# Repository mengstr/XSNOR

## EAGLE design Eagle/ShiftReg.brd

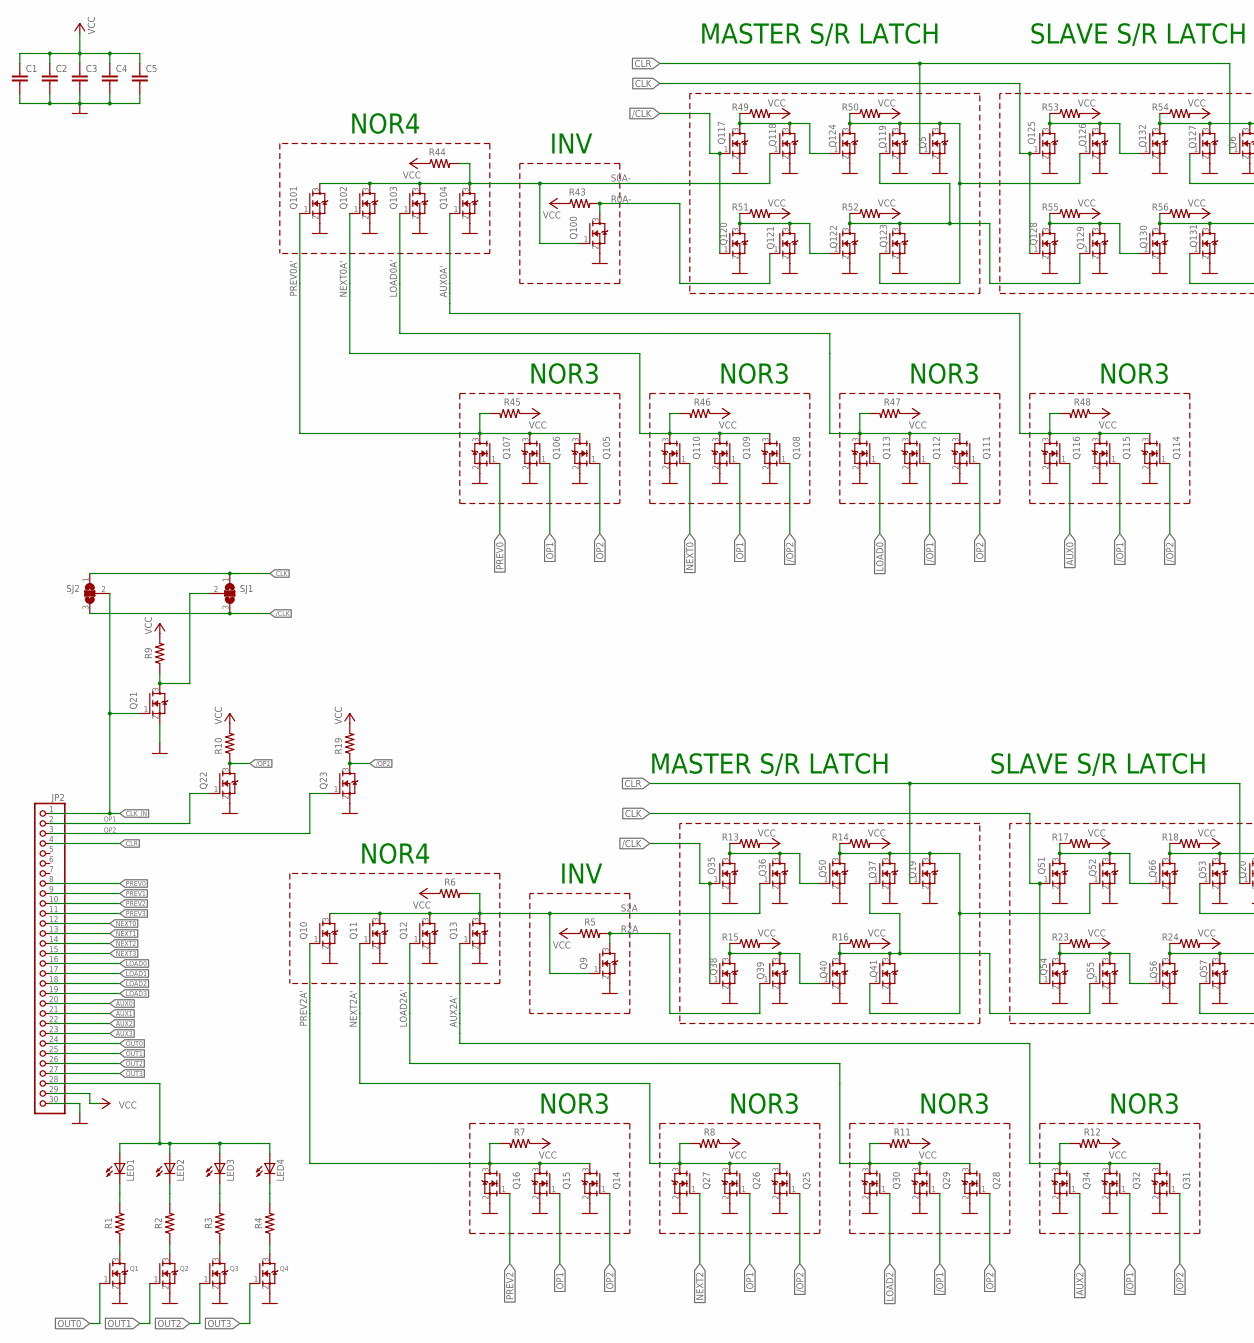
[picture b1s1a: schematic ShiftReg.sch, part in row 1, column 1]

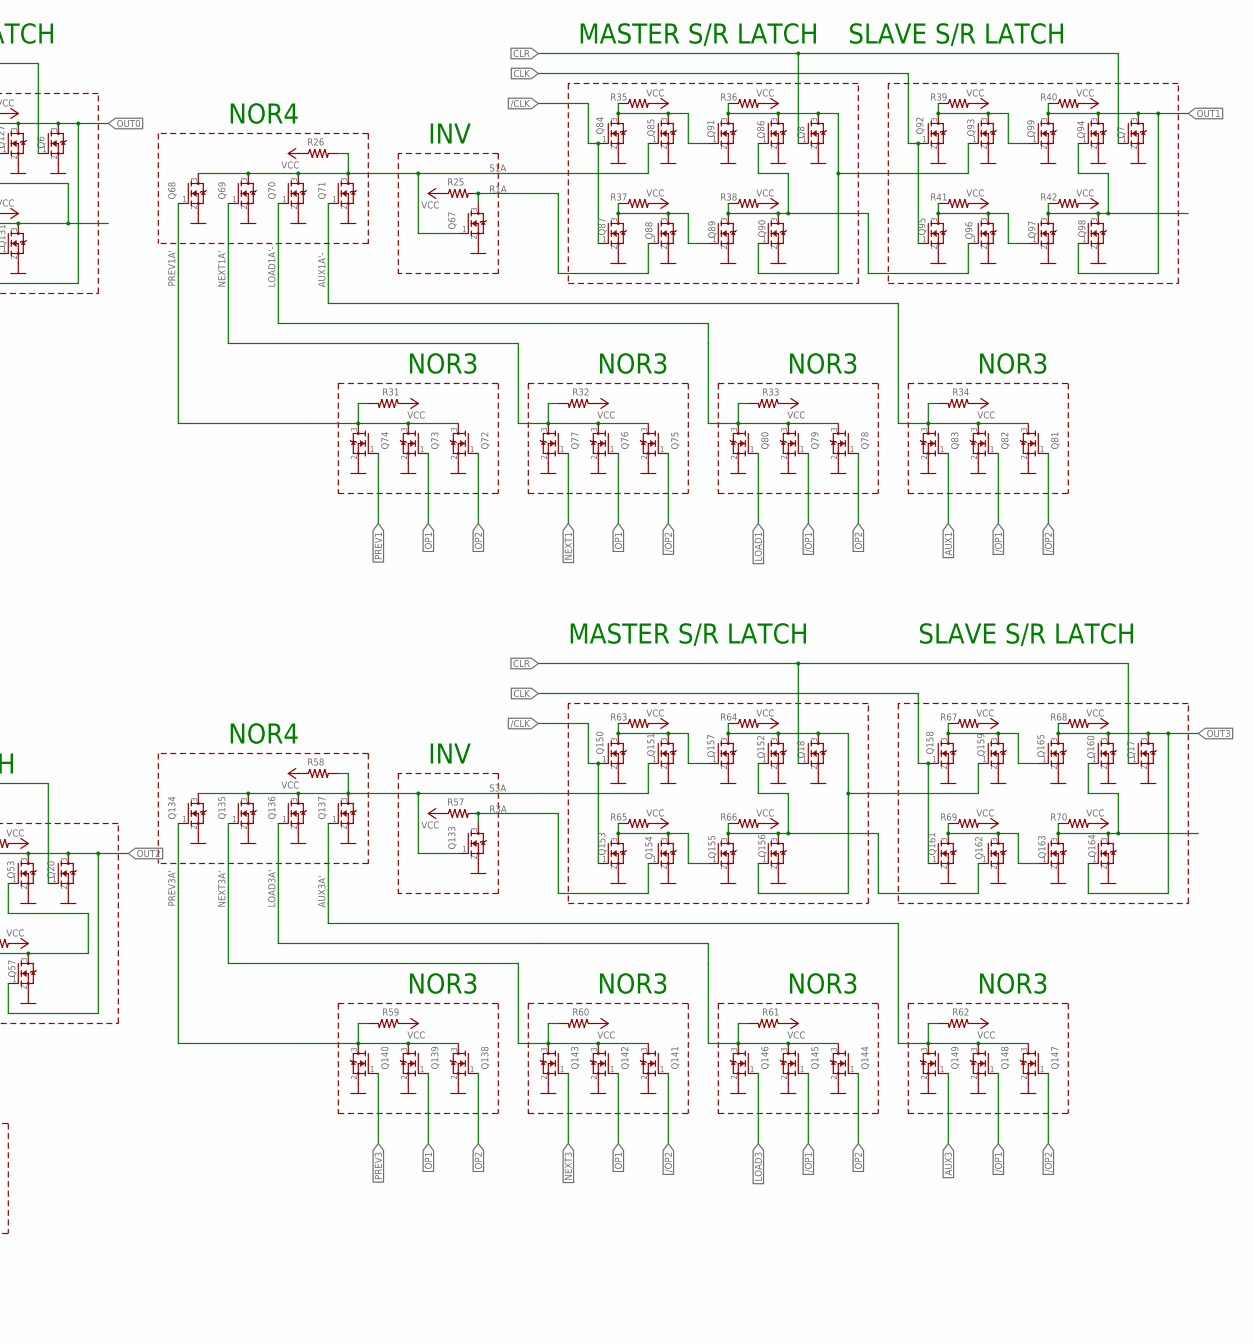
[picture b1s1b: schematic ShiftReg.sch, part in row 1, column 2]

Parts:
C1, C2, C3, C4, C5: C-EUC0805K; C0805K
JP2: PINHD-1X30; 1X30
LED1, LED2, LED3, LED4: LEDSQR2X5; LED2X5
Q1, Q2, Q3, Q4: NMOSREFLOW; SOT23
Q5, Q6, Q7, Q8, Q9, Q10, Q11, Q12, Q13, Q14, Q15, Q16, Q17, Q18, Q19, Q20, Q21, Q22, Q23, Q25, Q26, Q27, Q28, Q29, Q30, Q31, Q32, Q34, Q35, Q36, Q37, Q38, Q39, Q40, Q41, Q50, Q51, Q52, Q53, Q54, Q55, Q56, Q57, Q66, Q67, Q68, Q69, Q70, Q71, Q72, Q73, Q74, Q75, Q76, Q77, Q78, Q79, Q80, Q81, Q82, Q83, Q84, Q85, Q86, Q87, Q88, Q89, Q90, Q91, Q92, Q93, Q94, Q95, Q96, Q97, Q98, Q99, Q100, Q101, Q102, Q103, Q104, Q105, Q106, Q107, Q108, Q109, Q110, Q111, Q112, Q113, Q114, Q115, Q116, Q117, Q118, Q119, Q120, Q121, Q122, Q123, Q124, Q125, Q126, Q127, Q128, Q129, Q130, Q131, Q132, Q133, Q134, Q135, Q136, Q137, Q138, Q139, Q140, Q141, Q142, Q143, Q144, Q145, Q146, Q147, Q148, Q149, Q150, Q151, Q152, Q153, Q154, Q155, Q156, Q157, Q158, Q159, Q160, Q161, Q162, Q163, Q164, Q165: 310mA/60V/1.6Ω; SOT23
R1, R2, R3, R4, R5, R6, R7, R8, R9, R10, R11, R12, R13, R14, R15, R16, R17, R18, R19, R23, R24, R25, R26, R31, R32, R33, R34, R35, R36, R37, R38, R39, R40, R41, R42, R43, R44, R45, R46, R47, R48, R49, R50, R51, R52, R53, R54, R55, R56, R57, R58, R59, R60, R61, R62, R63, R64, R65, R66, R67, R68, R69, R70: 0805
SJ1, SJ2: SJ2W; SJ_2

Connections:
/CLK: Q35.1 (G), Q38.1 (G), Q84.1 (G), Q87.1 (G), Q117.1 (G), Q120.1 (G), Q150.1 (G), Q153.1 (G), SJ1.3, SJ2.3
/OP1: Q22.3 (D), Q29.1 (G), Q32.1 (G), Q79.1 (G), Q82.1 (G), Q112.1 (G), Q115.1 (G), Q145.1 (G), Q148.1 (G), R10.1
/OP2: Q23.3 (D), Q25.1 (G), Q31.1 (G), Q75.1 (G), Q81.1 (G), Q108.1 (G), Q114.1 (G), Q141.1 (G), Q147.1 (G), R19.1
AUX0: JP2.20, Q116.1 (G)
AUX0A': Q104.1 (G), Q114.3 (D), Q115.3 (D), Q116.3 (D), R48.2
AUX1: JP2.21, Q83.1 (G)
AUX1A'-: Q71.1 (G), Q81.3 (D), Q82.3 (D), Q83.3 (D), R34.2
AUX2: JP2.22, Q34.1 (G)
AUX2A': Q13.1 (G), Q31.3 (D), Q32.3 (D), Q34.3 (D), R12.2
AUX3: JP2.23, Q149.1 (G)
AUX3A': Q137.1 (G), Q147.3 (D), Q148.3 (D), Q149.3 (D), R62.2
CLK: Q51.1 (G), Q54.1 (G), Q92.1 (G), Q95.1 (G), Q125.1 (G), Q128.1 (G), Q158.1 (G), Q161.1 (G), SJ1.1, SJ2.1
CLK_IN: JP2.1, Q21.1 (G), SJ2.2
CLR: JP2.4, Q5.1 (G), Q6.1 (G), Q7.1 (G), Q8.1 (G), Q17.1 (G), Q18.1 (G), Q19.1 (G), Q20.1 (G)
GND: C1.2, C2.2, C3.2, C4.2, C5.2, JP2.30, Q1.2 (S), Q2.2 (S), Q3.2 (S), Q4.2 (S), Q5.2 (S), Q6.2 (S), Q7.2 (S), Q8.2 (S), Q9.2 (S), Q10.2 (S), Q11.2 (S), Q12.2 (S), Q13.2 (S), Q14.2 (S), Q15.2 (S), Q16.2 (S), Q17.2 (S), Q18.2 (S), Q19.2 (S), Q20.2 (S), Q21.2 (S), Q22.2 (S), Q23.2 (S), Q25.2 (S), Q26.2 (S), Q27.2 (S), Q28.2 (S), Q29.2 (S), Q30.2 (S), Q31.2 (S), Q32.2 (S), Q34.2 (S), Q35.2 (S), Q36.2 (S), Q37.2 (S), Q38.2 (S), Q39.2 (S), Q40.2 (S), Q41.2 (S), Q50.2 (S), Q51.2 (S), Q52.2 (S), Q53.2 (S), Q54.2 (S), Q55.2 (S), Q56.2 (S), Q57.2 (S), Q66.2 (S), Q67.2 (S), Q68.2 (S), Q69.2 (S), Q70.2 (S), Q71.2 (S), Q72.2 (S), Q73.2 (S), Q74.2 (S), Q75.2 (S), Q76.2 (S), Q77.2 (S), Q78.2 (S), Q79.2 (S), Q80.2 (S), Q81.2 (S), Q82.2 (S), Q83.2 (S), Q84.2 (S), Q85.2 (S), Q86.2 (S), Q87.2 (S), Q88.2 (S), Q89.2 (S), Q90.2 (S), Q91.2 (S), Q92.2 (S), Q93.2 (S), Q94.2 (S), Q95.2 (S), Q96.2 (S), Q97.2 (S), Q98.2 (S), Q99.2 (S), Q100.2 (S), Q101.2 (S), Q102.2 (S), Q103.2 (S), Q104.2 (S), Q105.2 (S), Q106.2 (S), Q107.2 (S), Q108.2 (S), Q109.2 (S), Q110.2 (S), Q111.2 (S), Q112.2 (S), Q113.2 (S), Q114.2 (S), Q115.2 (S), Q116.2 (S), Q117.2 (S), Q118.2 (S), Q119.2 (S), Q120.2 (S), Q121.2 (S), Q122.2 (S), Q123.2 (S), Q124.2 (S), Q125.2 (S), Q126.2 (S), Q127.2 (S), Q128.2 (S), Q129.2 (S), Q130.2 (S), Q131.2 (S), Q132.2 (S), Q133.2 (S), Q134.2 (S), Q135.2 (S), Q136.2 (S), Q137.2 (S), Q138.2 (S), Q139.2 (S), Q140.2 (S), Q141.2 (S), Q142.2 (S), Q143.2 (S), Q144.2 (S), Q145.2 (S), Q146.2 (S), Q147.2 (S), Q148.2 (S), Q149.2 (S), Q150.2 (S), Q151.2 (S), Q152.2 (S), Q153.2 (S), Q154.2 (S), Q155.2 (S), Q156.2 (S), Q157.2 (S), Q158.2 (S), Q159.2 (S), Q160.2 (S), Q161.2 (S), Q162.2 (S), Q163.2 (S), Q164.2 (S), Q165.2 (S)
LED+: JP2.28, LED1.A, LED2.A, LED3.A, LED4.A
LOAD0: JP2.16, Q113.1 (G)
LOAD0A': Q103.1 (G), Q111.3 (D), Q112.3 (D), Q113.3 (D), R47.2
LOAD1: JP2.17, Q80.1 (G)
LOAD1A'-: Q70.1 (G), Q78.3 (D), Q79.3 (D), Q80.3 (D), R33.2
LOAD2: JP2.18, Q30.1 (G)
LOAD2A': Q12.1 (G), Q28.3 (D), Q29.3 (D), Q30.3 (D), R11.2
LOAD3: JP2.19, Q146.1 (G)
LOAD3A': Q136.1 (G), Q144.3 (D), Q145.3 (D), Q146.3 (D), R61.2
unnamed: Q35.3 (D), Q36.3 (D), Q50.1 (G), R13.1
unnamed: Q38.3 (D), Q39.3 (D), Q40.1 (G), R15.1
unnamed: Q21.3 (D), R9.1, SJ1.2
unnamed: Q51.3 (D), Q52.3 (D), Q66.1 (G), R17.1
unnamed: Q1.3 (D), R1.1
unnamed: Q2.3 (D), R2.1
unnamed: Q54.3 (D), Q55.3 (D), Q56.1 (G), R23.1
unnamed: Q84.3 (D), Q85.3 (D), Q91.1 (G), R35.1
unnamed: Q87.3 (D), Q88.3 (D), Q89.1 (G), R37.1
unnamed: Q92.3 (D), Q93.3 (D), Q99.1 (G), R39.1
unnamed: Q95.3 (D), Q96.3 (D), Q97.1 (G), R41.1
unnamed: Q150.3 (D), Q151.3 (D), Q157.1 (G), R63.1
unnamed: Q153.3 (D), Q154.3 (D), Q155.1 (G), R65.1
unnamed: Q158.3 (D), Q159.3 (D), Q165.1 (G), R67.1
unnamed: Q161.3 (D), Q162.3 (D), Q163.1 (G), R69.1
unnamed: Q117.3 (D), Q118.3 (D), Q124.1 (G), R49.1
unnamed: Q120.3 (D), Q121.3 (D), Q122.1 (G), R51.1
unnamed: Q125.3 (D), Q126.3 (D), Q132.1 (G), R53.1
unnamed: Q128.3 (D), Q129.3 (D), Q130.1 (G), R55.1
unnamed: Q3.3 (D), R3.1
unnamed: Q4.3 (D), R4.1
unnamed: LED4.K (C), R4.2
unnamed: LED3.K (C), R3.2
unnamed: LED2.K (C), R2.2
unnamed: LED1.K (C), R1.2
unnamed: Q5.3 (D), Q119.3 (D), Q123.1 (G), Q124.3 (D), Q126.1 (G), R50.1
unnamed: Q119.1 (G), Q122.3 (D), Q123.3 (D), Q129.1 (G), R52.1
unnamed: Q127.1 (G), Q130.3 (D), Q131.3 (D), R56.1
unnamed: Q86.1 (G), Q89.3 (D), Q90.3 (D), Q96.1 (G), R38.1
unnamed: Q8.3 (D), Q86.3 (D), Q90.1 (G), Q91.3 (D), Q93.1 (G), R36.1
unnamed: Q94.1 (G), Q97.3 (D), Q98.3 (D), R42.1
unnamed: Q53.1 (G), Q56.3 (D), Q57.3 (D), R24.1
unnamed: Q37.1 (G), Q40.3 (D), Q41.3 (D), Q55.1 (G), R16.1
unnamed: Q19.3 (D), Q37.3 (D), Q41.1 (G), Q50.3 (D), Q52.1 (G), R14.1
unnamed: Q160.1 (G), Q163.3 (D), Q164.3 (D), R70.1
unnamed: Q152.1 (G), Q155.3 (D), Q156.3 (D), Q162.1 (G), R66.1
unnamed: Q18.3 (D), Q152.3 (D), Q156.1 (G), Q157.3 (D), Q159.1 (G), R64.1
NEXT0: JP2.12, Q110.1 (G)
NEXT0A': Q102.1 (G), Q108.3 (D), Q109.3 (D), Q110.3 (D), R46.2
NEXT1: JP2.13, Q77.1 (G)
NEXT1A': Q69.1 (G), Q75.3 (D), Q76.3 (D), Q77.3 (D), R32.2
NEXT2: JP2.14, Q27.1 (G)
NEXT2A': Q11.1 (G), Q25.3 (D), Q26.3 (D), Q27.3 (D), R8.2
NEXT3: JP2.15, Q143.1 (G)
NEXT3A': Q135.1 (G), Q141.3 (D), Q142.3 (D), Q143.3 (D), R60.2
OP1: JP2.2, Q15.1 (G), Q22.1 (G), Q26.1 (G), Q73.1 (G), Q76.1 (G), Q106.1 (G), Q109.1 (G), Q139.1 (G), Q142.1 (G)
OP2: JP2.3, Q14.1 (G), Q23.1 (G), Q28.1 (G), Q72.1 (G), Q78.1 (G), Q105.1 (G), Q111.1 (G), Q138.1 (G), Q144.1 (G)
OUT0: JP2.24, Q1.1 (G), Q6.3 (D), Q127.3 (D), Q131.1 (G), Q132.3 (D), R54.1
OUT1: JP2.25, Q2.1 (G), Q7.3 (D), Q94.3 (D), Q98.1 (G), Q99.3 (D), R40.1
OUT2: JP2.26, Q3.1 (G), Q20.3 (D), Q53.3 (D), Q57.1 (G), Q66.3 (D), R18.1
OUT3: JP2.27, Q4.1 (G), Q17.3 (D), Q160.3 (D), Q164.1 (G), Q165.3 (D), R68.1
PREV0: JP2.8, Q107.1 (G)
PREV0A': Q101.1 (G), Q105.3 (D), Q106.3 (D), Q107.3 (D), R45.2
PREV1: JP2.9, Q74.1 (G)
PREV1A': Q68.1 (G), Q72.3 (D), Q73.3 (D), Q74.3 (D), R31.2
PREV2: JP2.10, Q16.1 (G)
PREV2A': Q10.1 (G), Q14.3 (D), Q15.3 (D), Q16.3 (D), R7.2
PREV3: JP2.11, Q140.1 (G)
PREV3A': Q134.1 (G), Q138.3 (D), Q139.3 (D), Q140.3 (D), R59.2
R0A-: Q100.3 (D), Q121.1 (G), R43.2
R1A: Q67.3 (D), Q88.1 (G), R25.2
R2A: Q9.3 (D), Q39.1 (G), R5.2
R3A: Q133.3 (D), Q154.1 (G), R57.2
S0A-: Q100.1 (G), Q101.3 (D), Q102.3 (D), Q103.3 (D), Q104.3 (D), Q118.1 (G), R44.2
S1A: Q67.1 (G), Q68.3 (D), Q69.3 (D), Q70.3 (D), Q71.3 (D), Q85.1 (G), R26.2
S2A: Q9.1 (G), Q10.3 (D), Q11.3 (D), Q12.3 (D), Q13.3 (D), Q36.1 (G), R6.2
S3A: Q133.1 (G), Q134.3 (D), Q135.3 (D), Q136.3 (D), Q137.3 (D), Q151.1 (G), R58.2
VCC: C1.1, C2.1, C3.1, C4.1, C5.1, JP2.29, R5.1, R6.1, R7.1, R8.1, R9.2, R10.2, R11.1, R12.1, R13.2, R14.2, R15.2, R16.2, R17.2, R18.2, R19.2, R23.2, R24.2, R25.1, R26.1, R31.1, R32.1, R33.1, R34.1, R35.2, R36.2, R37.2, R38.2, R39.2, R40.2, R41.2, R42.2, R43.1, R44.1, R45.1, R46.1, R47.1, R48.1, R49.2, R50.2, R51.2, R52.2, R53.2, R54.2, R55.2, R56.2, R57.1, R58.1, R59.1, R60.1, R61.1, R62.1, R63.2, R64.2, R65.2, R66.2, R67.2, R68.2, R69.2, R70.2

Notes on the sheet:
INV
NOR4
MASTER S/R LATCH
SLAVE S/R LATCH
NOR3

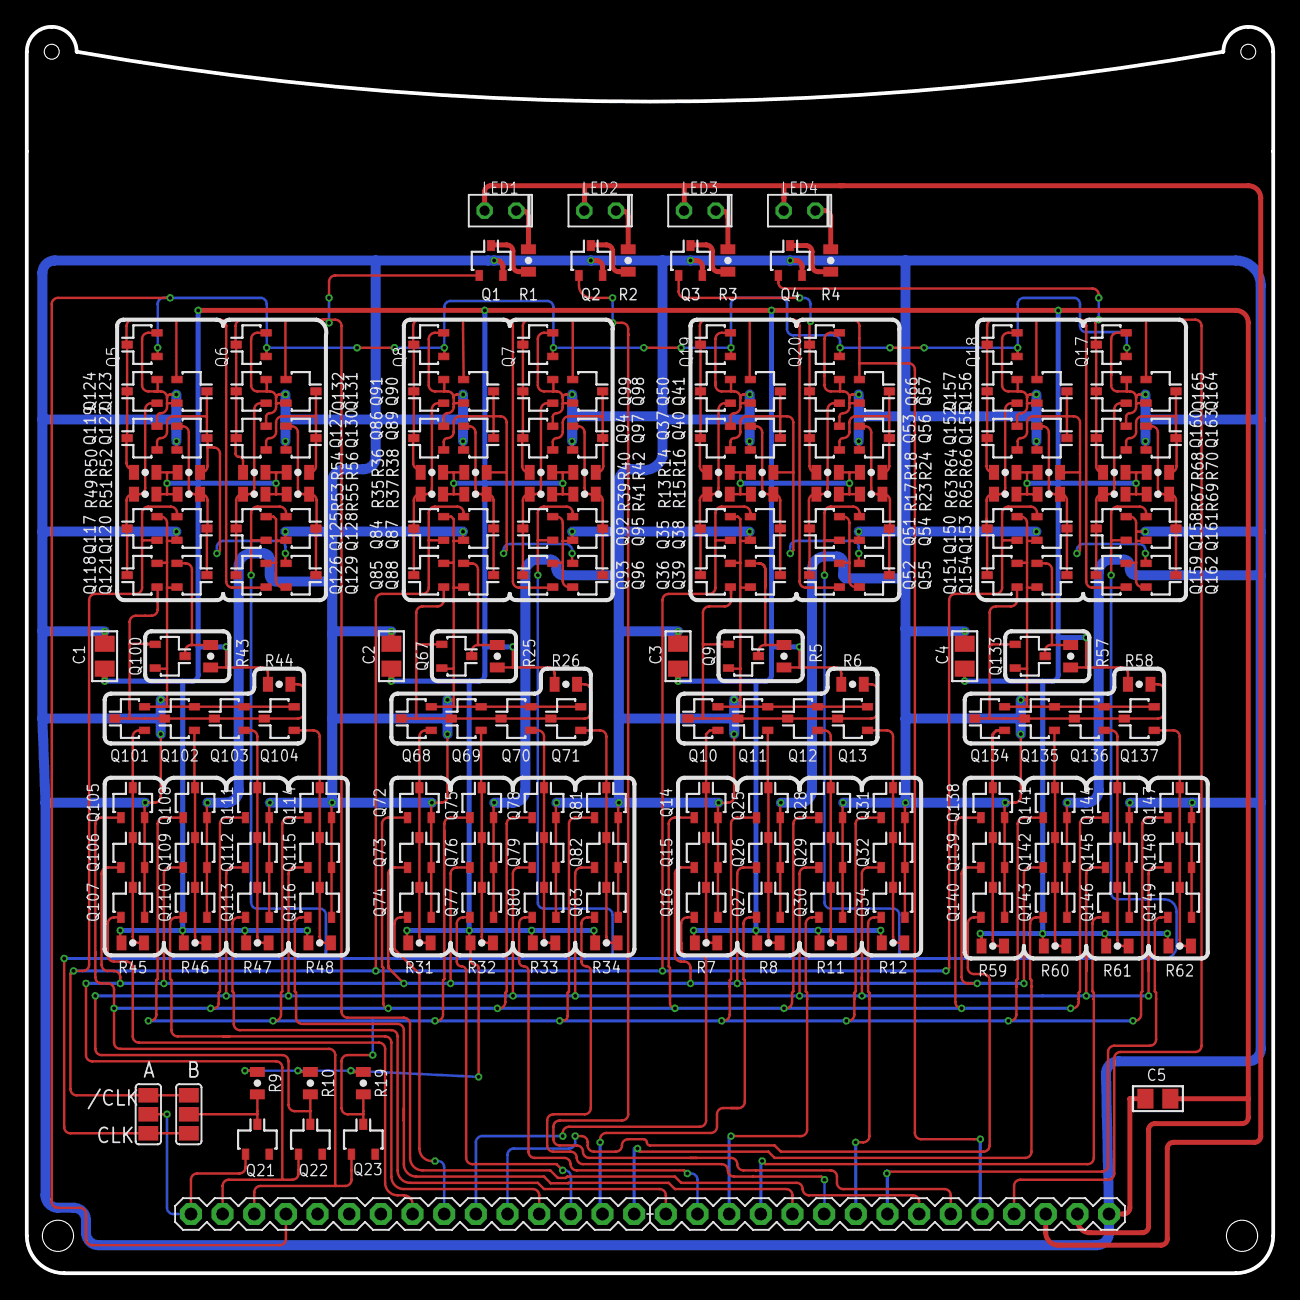
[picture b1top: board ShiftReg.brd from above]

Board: 2 copper layers, 100.0 x 100.0 mm, 222 parts (0 on the bottom side), 92 nets.

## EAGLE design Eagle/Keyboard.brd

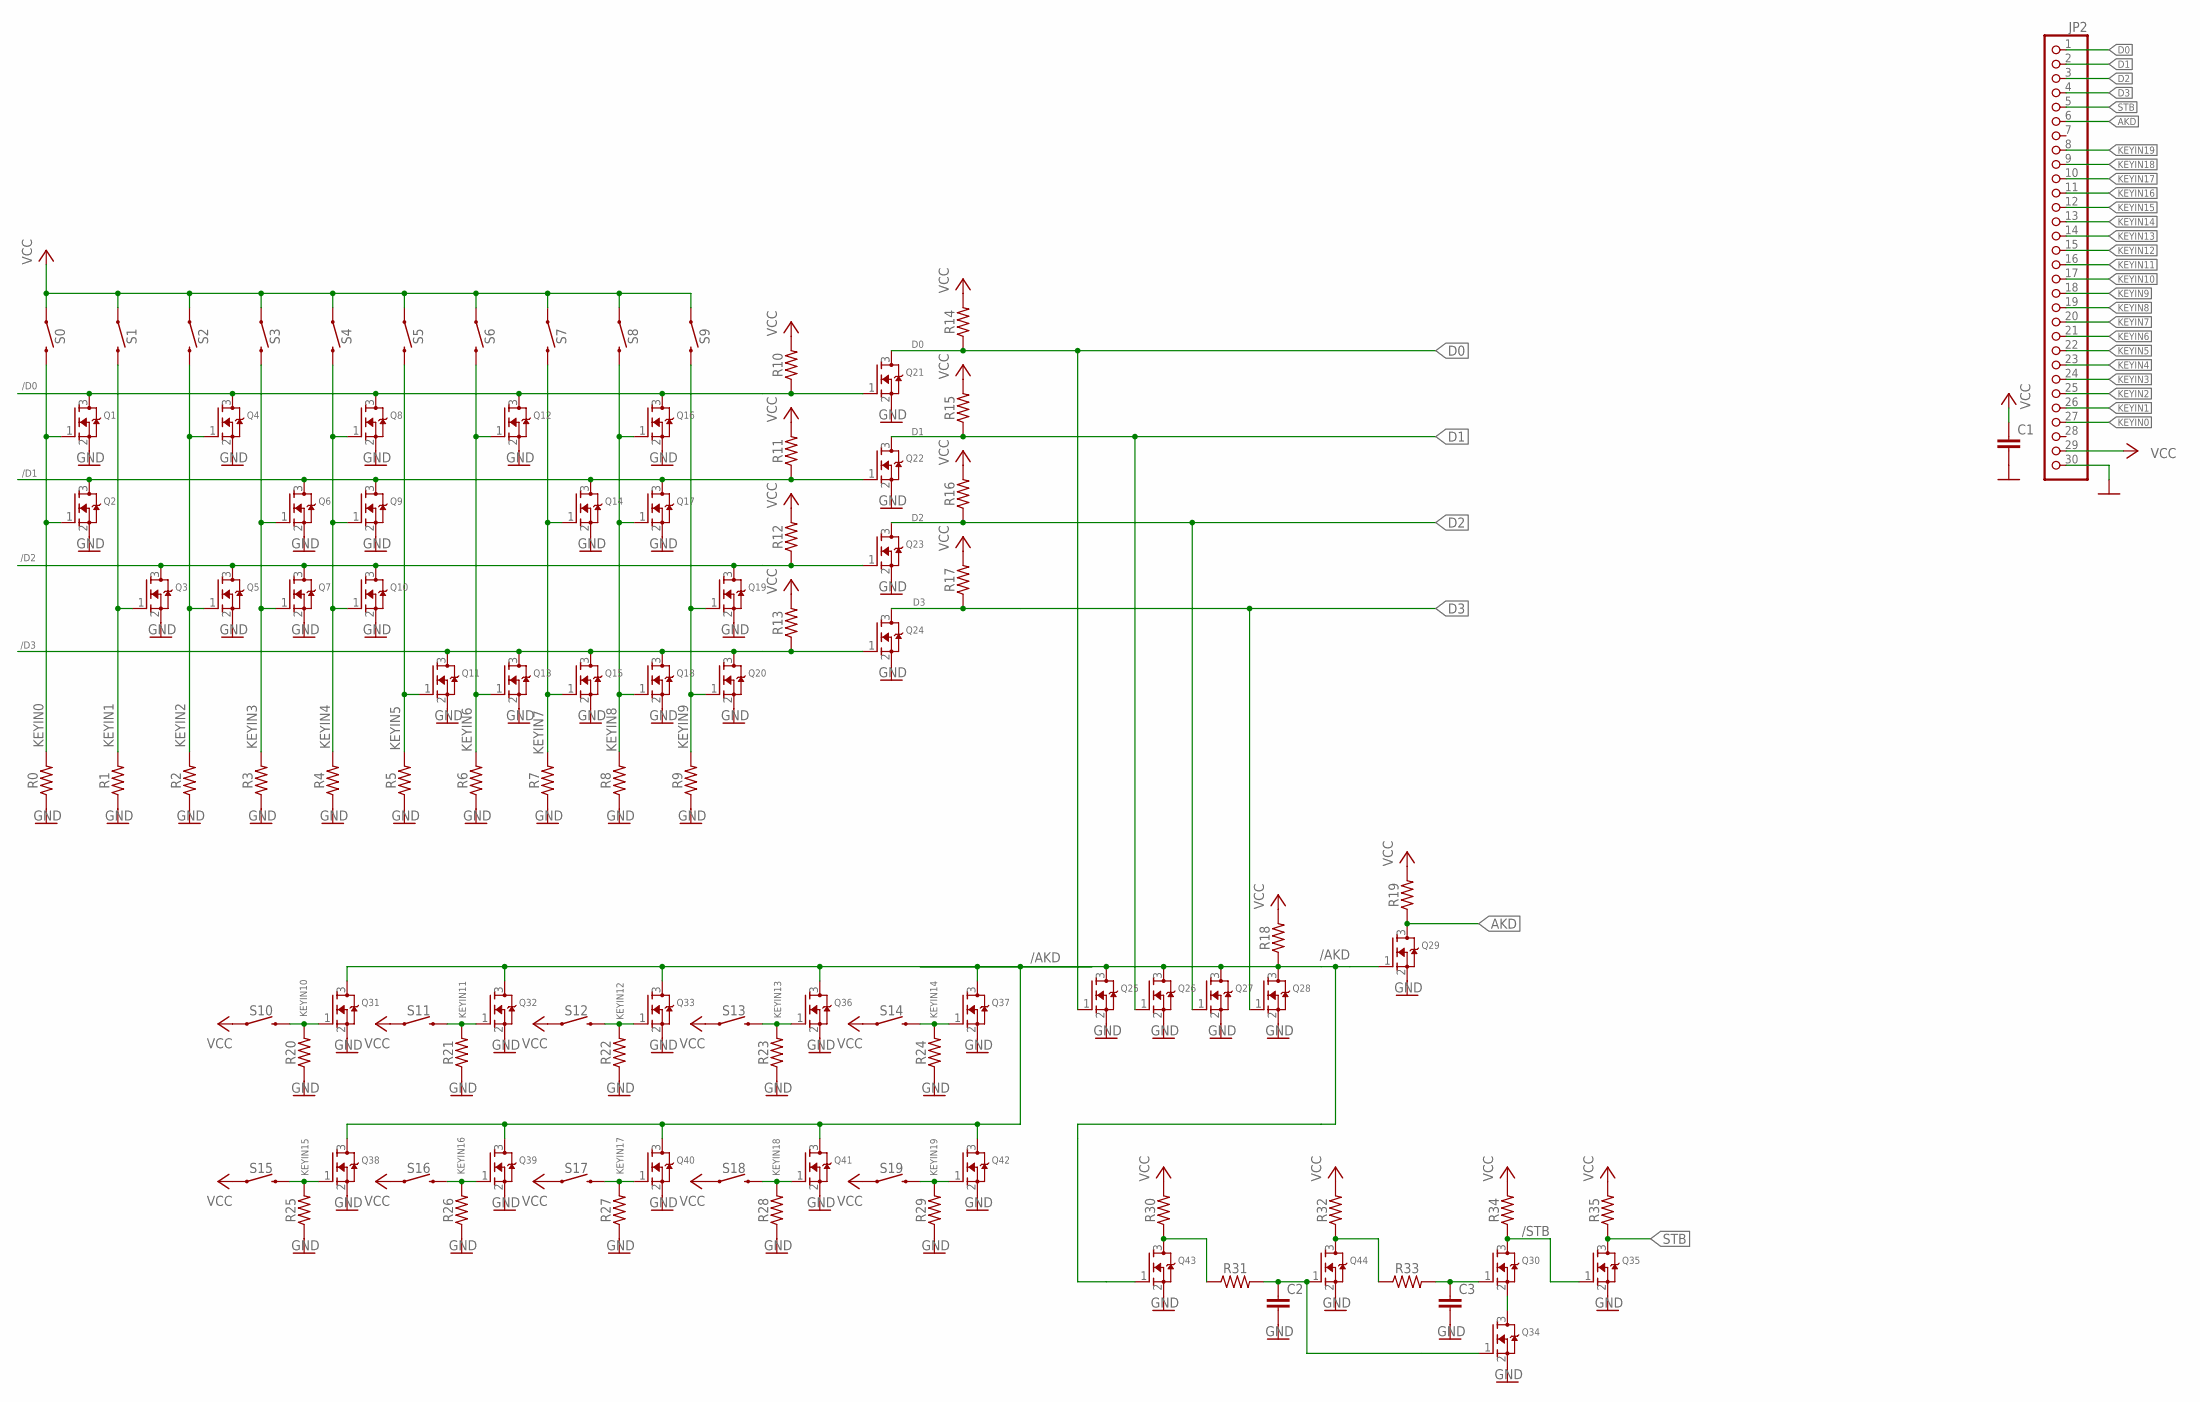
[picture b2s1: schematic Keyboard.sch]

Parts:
C1, C2, C3: C-EUC0805K; C0805K
JP2: PINHD-1X30; 1X30
Q1, Q2, Q3, Q4, Q5, Q6, Q7, Q8, Q9, Q10, Q11, Q12, Q13, Q14, Q15, Q16, Q17, Q18, Q19, Q20, Q21, Q22, Q23, Q24, Q25, Q26, Q27, Q28, Q29, Q30, Q31, Q32, Q33, Q34, Q35, Q36, Q37, Q38, Q39, Q40, Q41, Q42, Q43, Q44: NMOSREFLOW; SOT23
R0, R1, R2, R3, R4, R5, R6, R7, R8, R9, R10, R11, R12, R13, R14, R15, R16, R17, R18, R19, R20, R21, R22, R23, R24, R25, R26, R27, R28, R29, R30, R31, R32, R33, R34, R35: 0805
S0, S1, S2, S3, S4, S5, S6, S7, S8, S9, S10, S11, S12, S13, S14, S15, S16, S17, S18, S19: MOMENTARY-SWITCH-SPST-PTH-6.0MM; TACTILE_SWITCH_PTH_6.0MM

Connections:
/AKD: Q25.3 (D), Q26.3 (D), Q27.3 (D), Q28.3 (D), Q29.1 (G), Q31.3 (D), Q32.3 (D), Q33.3 (D), Q36.3 (D), Q37.3 (D), Q38.3 (D), Q39.3 (D), Q40.3 (D), Q41.3 (D), Q42.3 (D), Q43.1 (G), R18.1
/D0: Q1.3 (D), Q4.3 (D), Q8.3 (D), Q12.3 (D), Q16.3 (D), Q21.1 (G), R10.1
/D1: Q2.3 (D), Q6.3 (D), Q9.3 (D), Q14.3 (D), Q17.3 (D), Q22.1 (G), R11.1
/D2: Q3.3 (D), Q5.3 (D), Q7.3 (D), Q10.3 (D), Q19.3 (D), Q23.1 (G), R12.1
/D3: Q11.3 (D), Q13.3 (D), Q15.3 (D), Q18.3 (D), Q20.3 (D), Q24.1 (G), R13.1
/STB: Q30.3 (D), Q35.1 (G), R34.1
AKD: JP2.6, Q29.3 (D), R19.1
D0: JP2.1, Q21.3 (D), Q25.1 (G), R14.1
D1: JP2.2, Q22.3 (D), Q26.1 (G), R15.1
D2: JP2.3, Q23.3 (D), Q27.1 (G), R16.1
D3: JP2.4, Q24.3 (D), Q28.1 (G), R17.1
GND: C1.2, C2.2, C3.2, JP2.30, Q1.2 (S), Q2.2 (S), Q3.2 (S), Q4.2 (S), Q5.2 (S), Q6.2 (S), Q7.2 (S), Q8.2 (S), Q9.2 (S), Q10.2 (S), Q11.2 (S), Q12.2 (S), Q13.2 (S), Q14.2 (S), Q15.2 (S), Q16.2 (S), Q17.2 (S), Q18.2 (S), Q19.2 (S), Q20.2 (S), Q21.2 (S), Q22.2 (S), Q23.2 (S), Q24.2 (S), Q25.2 (S), Q26.2 (S), Q27.2 (S), Q28.2 (S), Q29.2 (S), Q31.2 (S), Q32.2 (S), Q33.2 (S), Q34.2 (S), Q35.2 (S), Q36.2 (S), Q37.2 (S), Q38.2 (S), Q39.2 (S), Q40.2 (S), Q41.2 (S), Q42.2 (S), Q43.2 (S), Q44.2 (S), R0.1, R1.1, R2.1, R3.1, R4.1, R5.1, R6.1, R7.1, R8.1, R9.1, R20.1, R21.1, R22.1, R23.1, R24.1, R25.1, R26.1, R27.1, R28.1, R29.1
KEYIN0: JP2.27, Q1.1 (G), Q2.1 (G), R0.2, S0.3 (2)
KEYIN1: JP2.26, Q3.1 (G), R1.2, S1.3 (2)
KEYIN2: JP2.25, Q4.1 (G), Q5.1 (G), R2.2, S2.3 (2)
KEYIN3: JP2.24, Q6.1 (G), Q7.1 (G), R3.2, S3.3 (2)
KEYIN4: JP2.23, Q8.1 (G), Q9.1 (G), Q10.1 (G), R4.2, S4.3 (2)
KEYIN5: JP2.22, Q11.1 (G), R5.2, S5.3 (2)
KEYIN6: JP2.21, Q12.1 (G), Q13.1 (G), R6.2, S6.3 (2)
KEYIN7: JP2.20, Q14.1 (G), Q15.1 (G), R7.2, S7.3 (2)
KEYIN8: JP2.19, Q16.1 (G), Q17.1 (G), Q18.1 (G), R8.2, S8.3 (2)
KEYIN9: JP2.18, Q19.1 (G), Q20.1 (G), R9.2, S9.3 (2)
KEYIN10: JP2.17, Q31.1 (G), R20.2, S10.3 (2)
KEYIN11: JP2.16, Q32.1 (G), R21.2, S11.3 (2)
KEYIN12: JP2.15, Q33.1 (G), R22.2, S12.3 (2)
KEYIN13: JP2.14, Q36.1 (G), R23.2, S13.3 (2)
KEYIN14: JP2.13, Q37.1 (G), R24.2, S14.3 (2)
KEYIN15: JP2.12, Q38.1 (G), R25.2, S15.3 (2)
KEYIN16: JP2.11, Q39.1 (G), R26.2, S16.3 (2)
KEYIN17: JP2.10, Q40.1 (G), R27.2, S17.3 (2)
KEYIN18: JP2.9, Q41.1 (G), R28.2, S18.3 (2)
KEYIN19: JP2.8, Q42.1 (G), R29.2, S19.3 (2)
unnamed: Q43.3 (D), R30.1, R31.1
unnamed: Q44.3 (D), R32.1, R33.1
unnamed: C3.1, Q30.1 (G), R33.2
unnamed: C2.1, Q34.1 (G), Q44.1 (G), R31.2
unnamed: Q30.2 (S), Q34.3 (D)
STB: JP2.5, Q35.3 (D), R35.1
VCC: C1.1, JP2.29, R10.2, R11.2, R12.2, R13.2, R14.2, R15.2, R16.2, R17.2, R18.2, R19.2, R30.2, R32.2, R34.2, R35.2, S0.1, S1.1, S2.1, S3.1, S4.1, S5.1, S6.1, S7.1, S8.1, S9.1, S10.1, S11.1, S12.1, S13.1, S14.1, S15.1, S16.1, S17.1, S18.1, S19.1

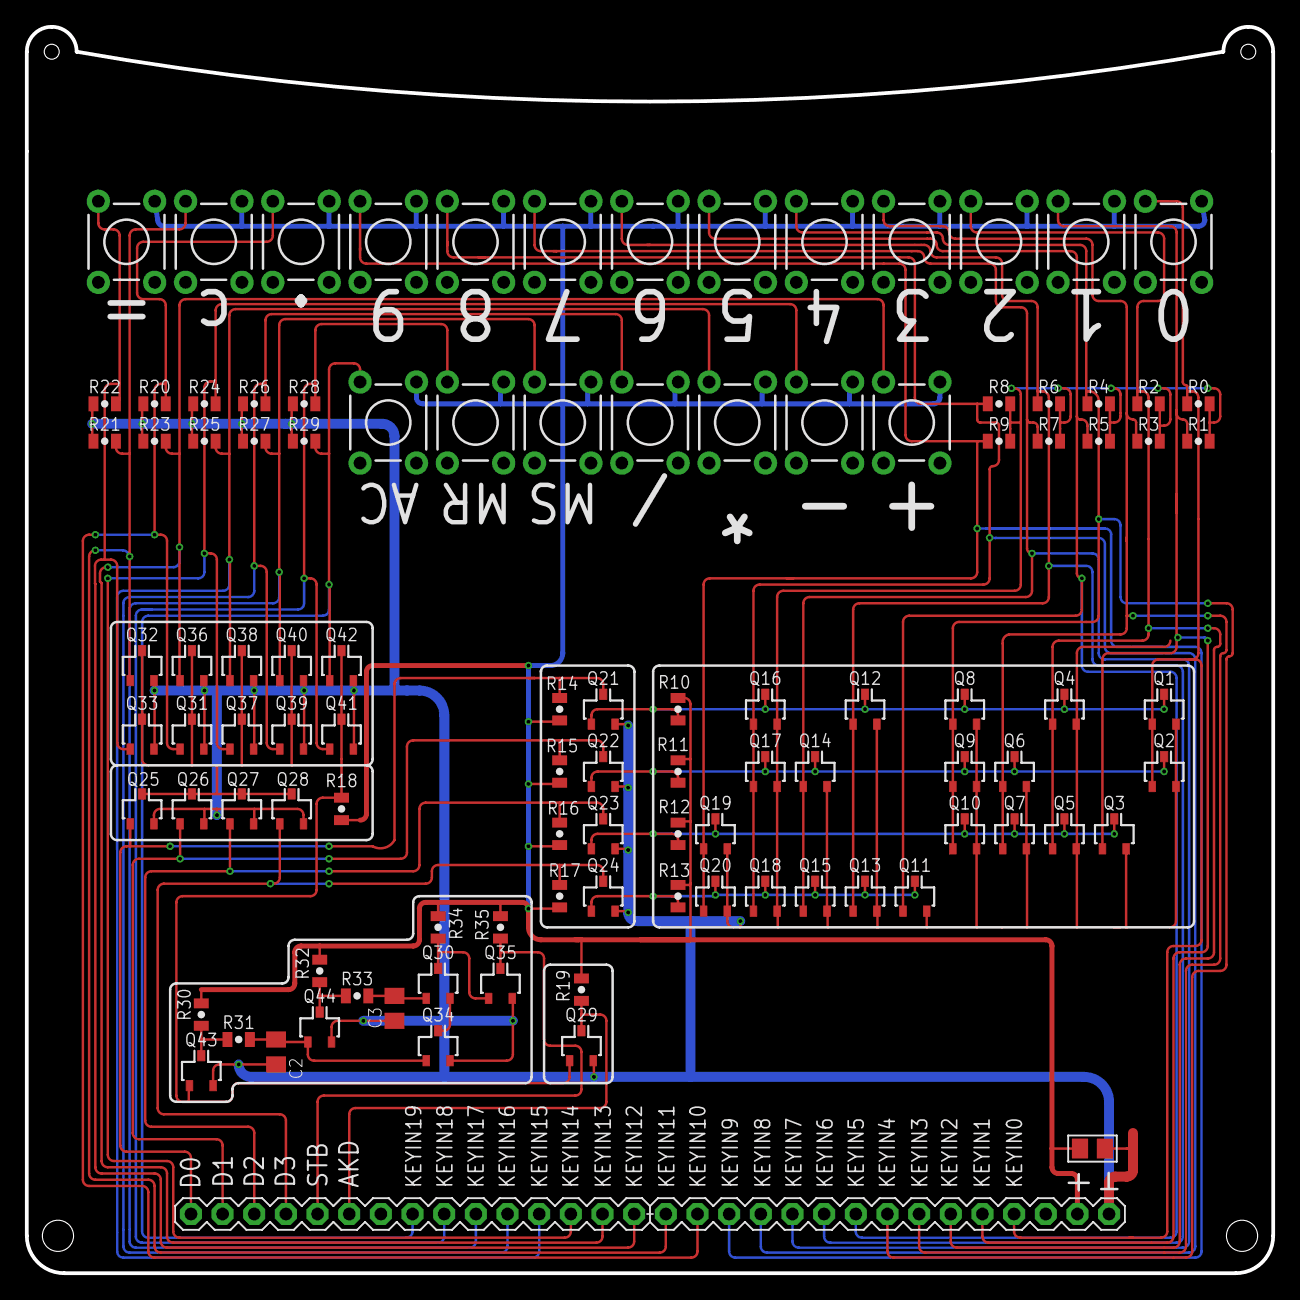
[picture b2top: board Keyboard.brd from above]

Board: 2 copper layers, 100.0 x 100.0 mm, 104 parts (0 on the bottom side), 39 nets.

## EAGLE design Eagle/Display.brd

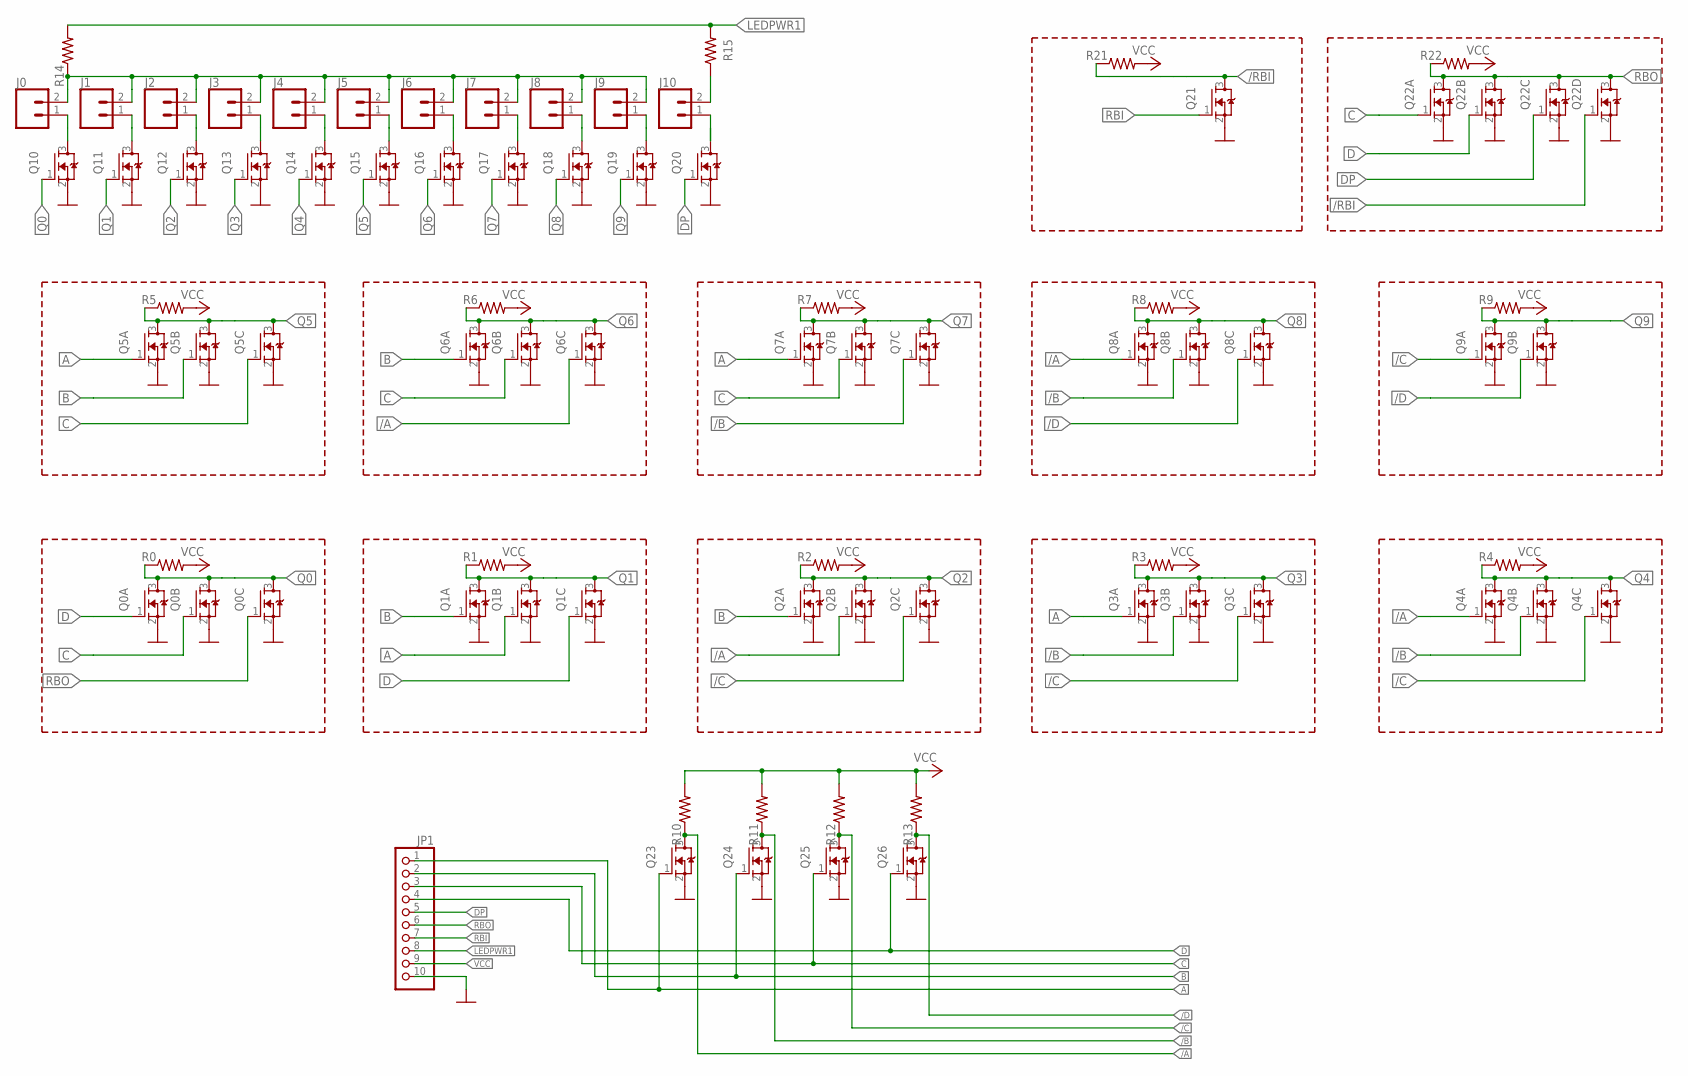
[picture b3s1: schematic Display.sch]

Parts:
J0, J1, J2, J3, J4, J5, J6, J7, J8, J9, J10: CONN_02; 1X02
JP1: PINHD-1X10/90; 1X10/90
Q0A, Q0B, Q0C, Q1A, Q1B, Q1C, Q2A, Q2B, Q2C, Q3A, Q3B, Q3C, Q4A, Q4B, Q4C, Q5A, Q5B, Q5C, Q6A, Q6B, Q6C, Q7A, Q7B, Q7C, Q8A, Q8B, Q8C, Q9A, Q9B, Q10, Q11, Q12, Q13, Q14, Q15, Q16, Q17, Q18, Q19, Q20, Q21, Q22A, Q22B, Q22C, Q22D, Q23, Q24, Q25, Q26: 310mA/60V/1.6Ω; SOT23
R0, R1, R2, R3, R4, R5, R6, R7, R8, R9, R10, R11, R12, R13, R14, R15, R21, R22: 0805

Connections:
/A: Q2B.1 (G), Q4A.1 (G), Q6C.1 (G), Q8A.1 (G), Q23.3 (D), R10.1
/B: Q3B.1 (G), Q4B.1 (G), Q7C.1 (G), Q8B.1 (G), Q24.3 (D), R11.1
/C: Q2C.1 (G), Q3C.1 (G), Q4C.1 (G), Q9A.1 (G), Q25.3 (D), R12.1
/D: Q8C.1 (G), Q9B.1 (G), Q26.3 (D), R13.1
/RBI: Q21.3 (D), Q22D.1 (G), R21.1
A: JP1.1, Q1B.1 (G), Q3A.1 (G), Q5A.1 (G), Q7A.1 (G), Q23.1 (G)
B: JP1.2, Q1A.1 (G), Q2A.1 (G), Q5B.1 (G), Q6A.1 (G), Q24.1 (G)
C: JP1.3, Q0B.1 (G), Q5C.1 (G), Q6B.1 (G), Q7B.1 (G), Q22A.1 (G), Q25.1 (G)
D: JP1.4, Q0A.1 (G), Q1C.1 (G), Q22B.1 (G), Q26.1 (G)
DP: JP1.5, Q20.1 (G), Q22C.1 (G)
GND: JP1.10, Q0A.2 (S), Q0B.2 (S), Q0C.2 (S), Q1A.2 (S), Q1B.2 (S), Q1C.2 (S), Q2A.2 (S), Q2B.2 (S), Q2C.2 (S), Q3A.2 (S), Q3B.2 (S), Q3C.2 (S), Q4A.2 (S), Q4B.2 (S), Q4C.2 (S), Q5A.2 (S), Q5B.2 (S), Q5C.2 (S), Q6A.2 (S), Q6B.2 (S), Q6C.2 (S), Q7A.2 (S), Q7B.2 (S), Q7C.2 (S), Q8A.2 (S), Q8B.2 (S), Q8C.2 (S), Q9A.2 (S), Q9B.2 (S), Q10.2 (S), Q11.2 (S), Q12.2 (S), Q13.2 (S), Q14.2 (S), Q15.2 (S), Q16.2 (S), Q17.2 (S), Q18.2 (S), Q19.2 (S), Q20.2 (S), Q21.2 (S), Q22A.2 (S), Q22B.2 (S), Q22C.2 (S), Q22D.2 (S), Q23.2 (S), Q24.2 (S), Q25.2 (S), Q26.2 (S)
LEDPWR: J0.2, J1.2, J2.2, J3.2, J4.2, J5.2, J6.2, J7.2, J8.2, J9.2, R14.1
LEDPWR1: JP1.8, R14.2, R15.2
unnamed: J0.1, Q10.3 (D)
unnamed: J1.1, Q11.3 (D)
unnamed: J2.1, Q12.3 (D)
unnamed: J3.1, Q13.3 (D)
unnamed: J4.1, Q14.3 (D)
unnamed: J5.1, Q15.3 (D)
unnamed: J6.1, Q16.3 (D)
unnamed: J7.1, Q17.3 (D)
unnamed: J10.2, R15.1
unnamed: J8.1, Q18.3 (D)
unnamed: J9.1, Q19.3 (D)
unnamed: J10.1, Q20.3 (D)
Q0: Q0A.3 (D), Q0B.3 (D), Q0C.3 (D), Q10.1 (G), R0.1
Q1: Q1A.3 (D), Q1B.3 (D), Q1C.3 (D), Q11.1 (G), R1.1
Q2: Q2A.3 (D), Q2B.3 (D), Q2C.3 (D), Q12.1 (G), R2.1
Q3: Q3A.3 (D), Q3B.3 (D), Q3C.3 (D), Q13.1 (G), R3.1
Q4: Q4A.3 (D), Q4B.3 (D), Q4C.3 (D), Q14.1 (G), R4.1
Q5: Q5A.3 (D), Q5B.3 (D), Q5C.3 (D), Q15.1 (G), R5.1
Q6: Q6A.3 (D), Q6B.3 (D), Q6C.3 (D), Q16.1 (G), R6.1
Q7: Q7A.3 (D), Q7B.3 (D), Q7C.3 (D), Q17.1 (G), R7.1
Q8: Q8A.3 (D), Q8B.3 (D), Q8C.3 (D), Q18.1 (G), R8.1
Q9: Q9A.3 (D), Q9B.3 (D), Q19.1 (G), R9.1
RBI: JP1.7, Q21.1 (G)
RBO: JP1.6, Q0C.1 (G), Q22A.3 (D), Q22B.3 (D), Q22C.3 (D), Q22D.3 (D), R22.1
VCC: JP1.9, R0.2, R1.2, R2.2, R3.2, R4.2, R5.2, R6.2, R7.2, R8.2, R9.2, R10.2, R11.2, R12.2, R13.2, R21.2, R22.2

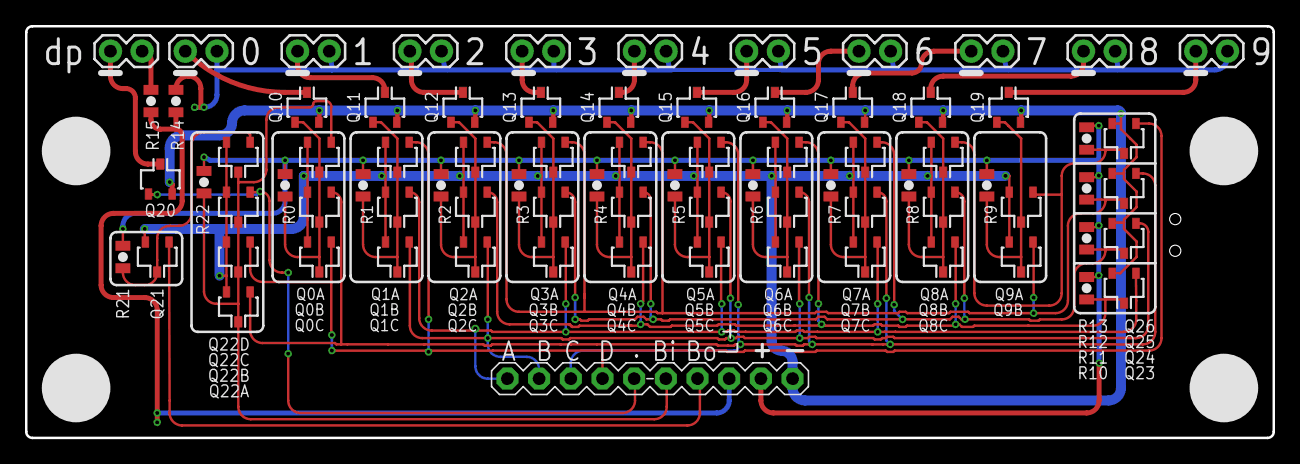
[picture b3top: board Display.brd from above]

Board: 2 copper layers, 100.0 x 33.0 mm, 79 parts (0 on the bottom side), 38 nets.

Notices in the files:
parts and their libraries:
SparkFun-Connectors: Licensing: Creative Commons ShareAlike 4.0 International - https://creativecommons.org/licenses/by-sa/4.0
